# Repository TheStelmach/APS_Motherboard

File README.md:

# PeekAntenna

Render 1

Render 2

Board partially assembled and debugged

Board communicated with by the custom RS-485 transceiver board, link below.

https://github.com/TheStelmach/UART_to_RS-485_V1/tree/main

Schematics Overview

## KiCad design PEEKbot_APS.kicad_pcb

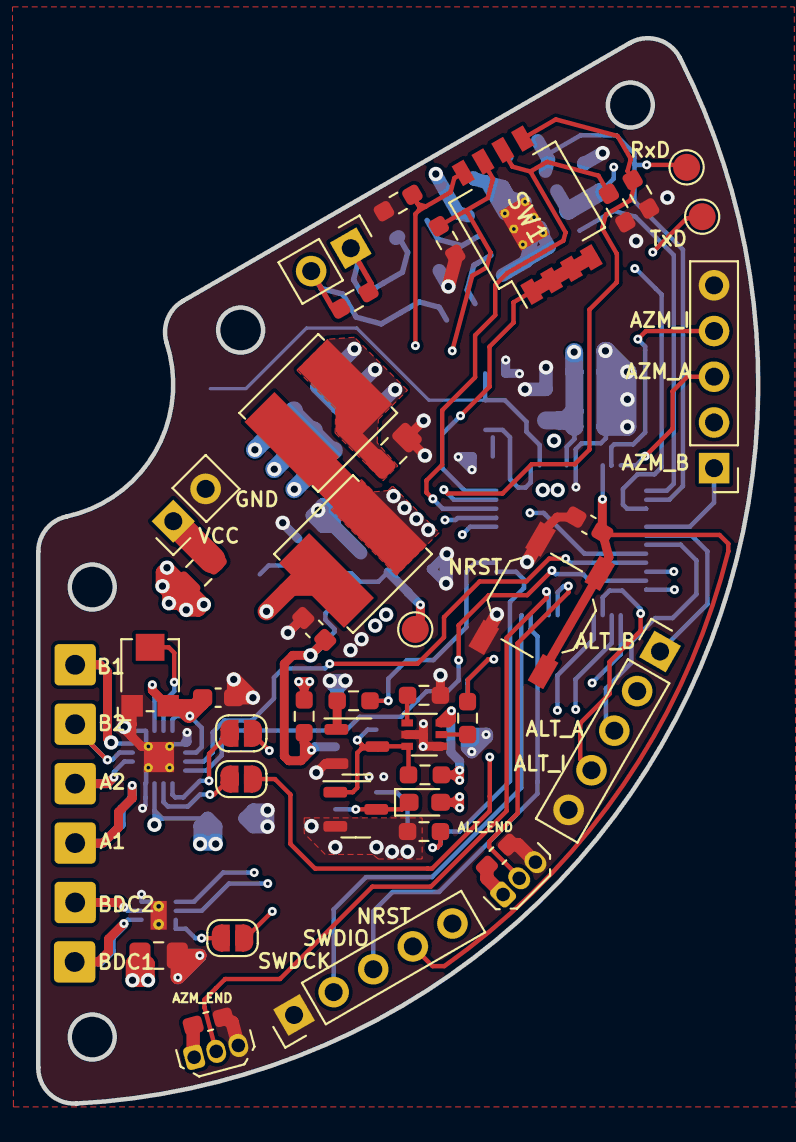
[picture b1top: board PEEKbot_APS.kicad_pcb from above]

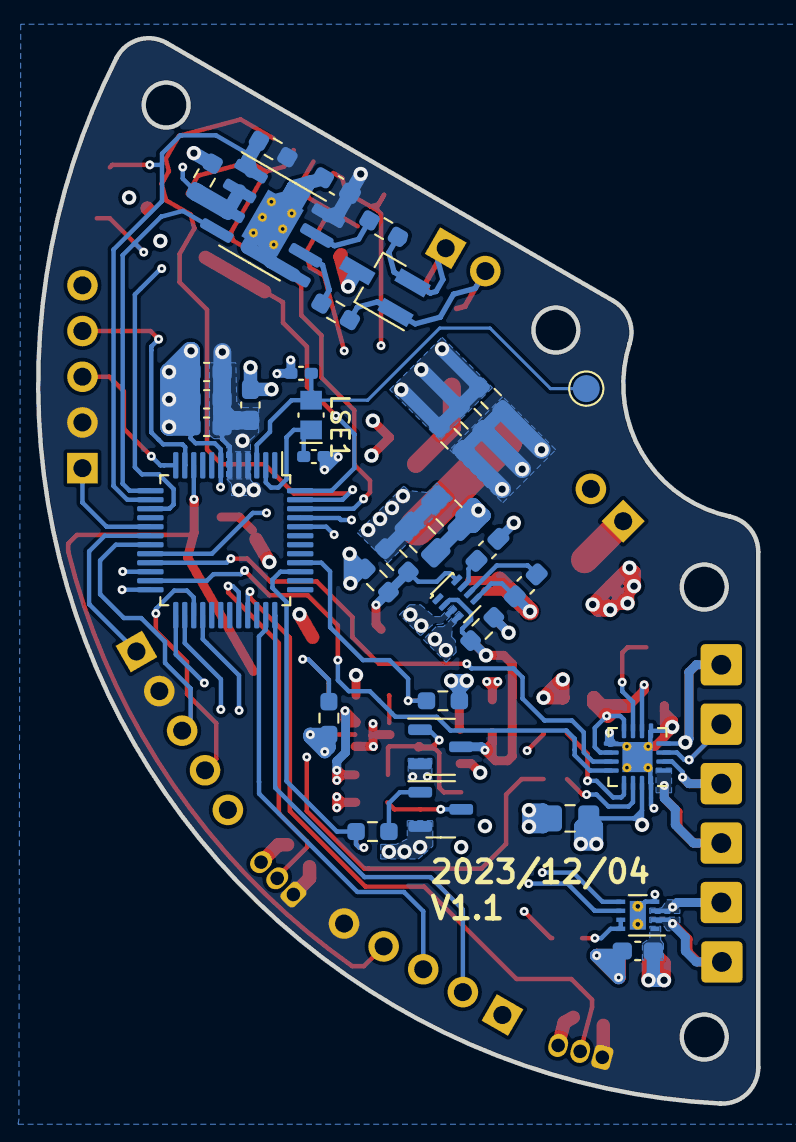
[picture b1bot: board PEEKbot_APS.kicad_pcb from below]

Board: 4 copper layers, 40.0 x 59.2 mm, 83 parts (36 on the bottom side), 63 nets.

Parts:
C1, C3: 15pF; C_0402_1005Metric_Pad0.74x0.62mm_HandSolder
C2, C4, C5, C6, C8, C10, C13, C14, C16, C19: 100nF; C_0603_1608Metric_Pad1.08x0.95mm_HandSolder
C7, C9: 4.7uF; C_0603_1608Metric_Pad1.08x0.95mm_HandSolder
C11: 0.47uF; C_0603_1608Metric_Pad1.08x0.95mm_HandSolder
C12, C15, C17, C18, C20: 22uF; C_0805_2012Metric_Pad1.18x1.45mm_HandSolder
ESD1: SM712_SOT23; SOT-23_Handsoldering
F1: Fuse; C_0805_2012Metric_Pad1.18x1.45mm_HandSolder
H1, H2, H3, H4, H5, H6: MountingHole_Pad; SolderWire-0.5sqmm_1x01_D0.9mm_OD2.3mm
J1, J5: Conn_01x02; PinHeader_1x02_P2.54mm_Vertical
J2: Conn_01x05; PinHeader_1x05_P2.54mm_Vertical
J3, J4: 0705430109; PinHeader_1x05_P2.54mm_Vertical
JP3, JP4, JP5: SolderJumper_2_Open; SolderJumper-2_P1.3mm_Open_RoundedPad1.0x1.5mm
L1, L2: 6.3uH; L_Bourns_SRN6045TA
LSE1: ECS-.327-12.5-16-TR3; Crystal_SMD_MicroCrystal_CM9V-T1A-2Pin_1.6x1.0mm_HandSolder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
Q1, Q2, Q3, Q4: 2N7002LT3G; SOT-23-3
R1, R2, R5, R6, R7, R8, R10, R12, R14, R15, R16, R17, R18, R19, R21: 10k; R_0603_1608Metric_Pad0.98x0.95mm_HandSolder
R3, R4: 10; R_0603_1608Metric_Pad0.98x0.95mm_HandSolder
R9: 30k; R_0603_1608Metric_Pad0.98x0.95mm_HandSolder
R11, R20: 31.3k; R_0603_1608Metric_Pad0.98x0.95mm_HandSolder
R13: Heater; LED_0603_1608Metric_Pad1.05x0.95mm_HandSolder
R22, R23, R24: 0; R_0603_1608Metric_Pad0.98x0.95mm_HandSolder
R25: 50; R_0603_1608Metric_Pad0.98x0.95mm_HandSolder
S1: PTS526; SW_SPST_TL3342
SW1: SW_DIP_x04; SW_DIP_SPSTx04_Slide_KingTek_DSHP04TS_W7.62mm_P1.27mm
TP1, TP2, TP3, TP4: TestPoint_Probe; TestPoint_Pad_D1.5mm
U1: SN65HVD72DRBR; SOIC-8-1EP_3.9x4.9mm_P1.27mm_EP2.29x3mm_ThermalVias
U2, U4: DRV5011; TO-92Flat
U3: STM32G071CBT6; LQFP-48_7x7mm_P0.5mm
U5: TMP300; SOT-363_SC-70-6
U6: DRV8428; WQFN-16-1EP_3x3mm_P0.5mm_EP1.68x1.68mm_ThermalVias
U7: TPS62933; SOT-583-8
U8: DRV8220DSGR-8p; WSON-8-1EP_2x2mm_P0.5mm_EP0.9x1.6mm_ThermalVias
VR1: TC33X-2-303E; Potentiometer_Bourns_TC33X_Vertical

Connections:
+3V3: C4.1, C5.1, C6.1, C7.1, C8.1, C9.1, C10.1, J2.5, J3.2, J4.2, R2.1, R22.1, R23.1, R24.1, U1.8 (VCC), U2.1 (VCC), U3.4 (VBAT), U3.5 (VREF+), U3.6 (VDD), U4.1 (VCC)
+12V: C12.1, C18.2, C19.2, F1.2, R12.1, R13.2, R16.1, U5.6 (V+), U6.15 (VM), U7.3 (VIN), U8.1 (VM)
BDC_DIR: U3.26 (PB14), U8.6 (IN1/PH)
BDC_PWM: U3.28 (PA8), U8.5 (IN2/EN)
BDC_nSLEEP: JP5.1 (A), U3.25 (PB13)
CFG1: R5.1, SW1.5, U3.47 (PB8)
CFG2: R6.1, SW1.6, U3.46 (PB7)
CFG3: R7.1, SW1.7, U3.45 (PB6)
CFG4: R8.1, SW1.8, U3.44 (PB5)
CFG_PWR: SW1.1, SW1.2, SW1.3, SW1.4, U3.48 (PB9)
EN: C13.1, Q3.3 (D), R16.2, R19.1, U7.2 (EN)
ENC_A_ALT: J4.3, U3.19 (PB0)
ENC_A_AZM: J3.3, U3.12 (PA1)
ENC_B_ALT: J4.1, U3.18 (PA7)
ENC_B_AZM: J3.1, U3.17 (PA6)
ENC_I_ALT: J4.4, U3.27 (PB15)
ENC_I_AZM: J3.4, U3.11 (PA0)
END_ALT: U3.32 (PA10/UCPD1_DBCC2), U4.2 (OUT)
END_AZM: U2.2 (OUT), U3.33 (PA11/PA9)
FB-3.3V: R20.1, R21.1, TP2.1, U7.8 (FB)
GND: C1.2, C2.2, C3.2, C4.2, C5.2, C6.2, C7.2, C8.2, C9.2, C10.2, C11.1, C12.2, C13.2, C15.2, C16.2, C17.2, C18.1, C19.1, C20.2, ESD1.3 (common), J2.1, J3.5, J4.5, J5.2, Q1.2 (S), Q2.2 (S), Q3.2 (S), Q4.2 (S), R1.2, R5.2, R6.2, R7.2, R8.2, R10.2, R11.1, R14.2, R18.2, R19.2, R21.2, S1.2 (NO), U1.5 (GND), U1.9 (EPAD), U2.3 (GND), U3.7 (VSS), U4.3 (GND), U5.2 (GND), U5.4 (HYSTSET), U6.5 (GND), U6.9 (DECAY_TOFF), U6.16 (PGND), U6.17 (PAD), U7.4 (GND), U8.4 (GND), U8.9 (GND), VR1.1 (CCW)
HEAT: R17.1, R18.1, U3.39 (PD1)
LPUART_DE: R1.1, U1.2 (*RE), U1.3 (DE), U3.15 (PA4)
LP_RxD: R2.2, TP4.1, U1.1 (R), U3.14 (PA3)
LP_TxD: TP3.1, U1.4 (D), U3.13 (PA2)
LSE_IN: C1.1, LSE1.1, U3.2 (PC14)
LSE_OUT: C3.1, LSE1.2, TP1.1, U3.3 (PC15)
MOFF: R14.1, R15.2, U3.40 (PD2)
NRST: C2.1, J2.4, S1.1 (COM), U3.10 (PF2)
unnamed: C15.1, C17.1, L1.2, L2.1, R20.2
unnamed: C20.1, L2.2, R22.2, R23.2, R24.2
unnamed: JP3.2 (B), U6.13 (EN_FAULT_N)
unnamed: JP4.2 (B), U6.14 (SLEEP_N)
unnamed: JP5.2 (B), U8.7 (MODE), U8.8 (nSLEEP)
unnamed: Q1.3 (D), Q4.3 (D), R13.1
unnamed: Q1.1 (G), Q2.3 (D), Q3.1 (G), R12.2, U5.3 (*OUT)
unnamed: Q2.1 (G), R15.1
unnamed: Q4.1 (G), R17.2
unnamed: R3.2, U1.6 (A)
unnamed: R4.2, U1.7 (B)
unnamed: R11.2, U5.1 (TSET)
unnamed: R9.1, U5.5 (VTEMP)
unnamed: H1.1, U6.1 (AOUT1)
unnamed: H3.1, U6.2 (AOUT2)
unnamed: H4.1, U6.4 (BOUT1)
unnamed: H2.1, U6.3 (BOUT2)
unnamed: U6.7 (VREF), VR1.2 (WIPER)
unnamed: C14.2, U7.6 (BST)
unnamed: C16.1, U7.7 (SS)
unnamed: C14.1, L1.1, U7.5 (SW)
unnamed: H5.1, U8.2 (OUT1)
unnamed: H6.1, U8.3 (OUT2)
OUT_A: ESD1.1 (A1), J1.2, R3.1, R25.1
OUT_B: ESD1.2 (A2), J1.1, R4.1, R25.2
STEP_DIR: U3.23 (PB11), U6.12 (DIR)
STEP_DVDD: C11.2, U6.6 (DVDD), U6.8 (M0), U6.10 (M1), VR1.3 (CW)
STEP_FAULT: JP3.1 (A), U3.20 (PB1)
STEP_PWM: U3.21 (PB2), U6.11 (STEP)
STEP_nSLEEP: JP4.1 (A), U3.24 (PB12)
SWDCLK: J2.2, U3.36 (PA14)
SWDIO: J2.3, U3.35 (PA13)
TEMP: R9.2, R10.1, U3.22 (PB10)
VCC: F1.1, J5.1

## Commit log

2023-10-08 Add files via upload
    H-bridges for BDC motors replaced with simple BLDC motor drivers (speed control only);
    Some 0 Ohm resistors replaced with bridge pads;
    All footprints assigned to components (Need to be reviewed, some footprints should be smaller);
    Started working on the PCB design
2024-01-11 Add files via upload
    1st iteration finalized. The board has been tested and partially debugged. Comments can be found in the txt file.
